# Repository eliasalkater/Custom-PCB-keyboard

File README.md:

# Custom-Mechanical-keyboard

Project: Custom Mechanical Keyboard

Goal: Design and build a fully functional mechanical keyboard, including a custom PCB and a custom 3D-printed case, designed to increase efficiency while programming.

Constraints:

    -Must be USB-C
    -Custom PCB
    -Custom case
    -3D printable
    -Reasonable cost
    -Functional firmware
    -Must be possible to manufacture with the tools available to me (JLCPCB)

A successful project is a keyboard where every key registers correctly, the PCB operates reliably, the case can be manufactured without significant post-processing, and the PCB, plate and case fit together without modification.

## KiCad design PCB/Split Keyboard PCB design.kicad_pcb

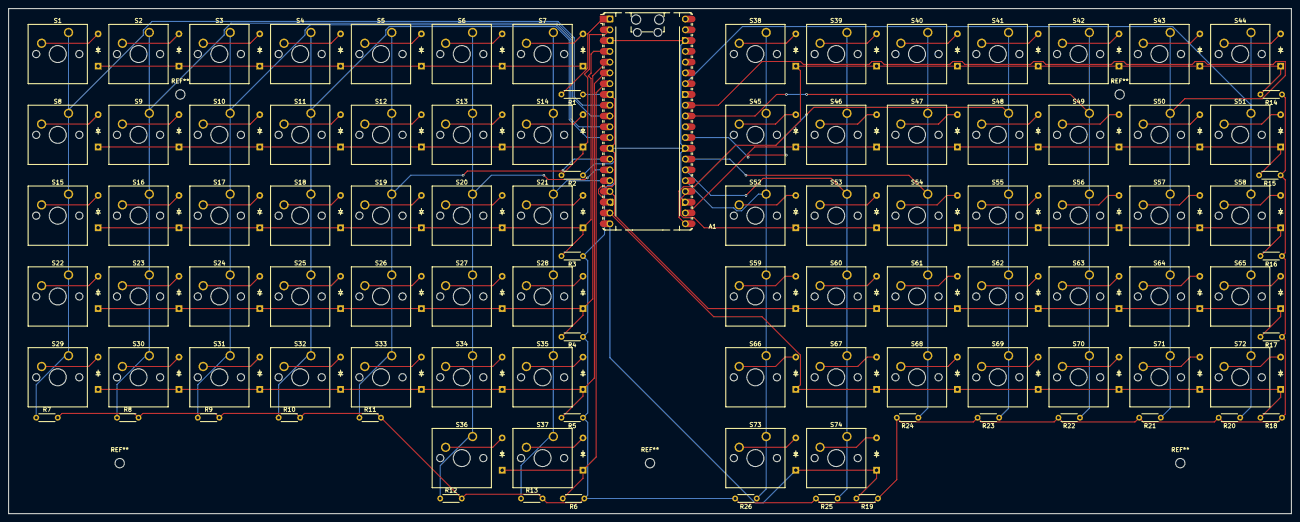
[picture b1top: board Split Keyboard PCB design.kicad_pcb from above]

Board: 2 copper layers, 302.4 x 119.1 mm, 175 parts (0 on the bottom side), 101 nets.

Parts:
A1: RaspberryPi_Pico; RaspberryPi_Pico_Common_Unspecified
D1, D2, D3, D4, D5, D6, D7, D8, D9, D10, D11, D12, D13, D14, D15, D16, D17, D18, D19, D20, D21, D22, D23, D24, D25, D26, D27, D28, D29, D30, D31, D32, D33, D34, D35, D36, D37, D38, D39, D40, D41, D42, D43, D44, D45, D46, D47, D48, D49, D50, D51, D52, D53, D54, D55, D56, D57, D58, D59, D60, D61, D62, D63, D64, D65, D66, D67, D68, D69, D70, D71, D72, D73, D74: Diode_DO-35
R1, R2, R3, R4, R5, R6, R7, R8, R9, R10, R11, R12, R13, R14, R15, R16, R17, R18, R19, R20, R21, R22, R23, R24, R25, R26: Resistor; R_Axial_DIN0204_L3.6mm_D1.6mm_P5.08mm_Horizontal
S1, S2, S3, S4, S5, S6, S7, S8, S9, S10, S11, S12, S13, S14, S15, S16, S17, S18, S19, S20, S21, S22, S23, S24, S25, S26, S27, S28, S29, S30, S31, S32, S33, S34, S35, S36, S37, S38, S39, S40, S41, S42, S43, S44, S45, S46, S47, S48, S49, S50, S51, S52, S53, S54, S55, S56, S57, S58, S59, S60, S61, S62, S63, S64, S65, S66, S67, S68, S69, S70, S71, S72, S73, S74: SW_Cherry_MX_1.00u_PCB

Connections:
Col 1: A1.9 (GPIO6), R7.1, S1.1, S8.1, S15.1, S22.1, S29.1
Col 2: A1.10 (GPIO7), R8.1, S2.1, S9.1, S16.1, S23.1, S30.1
Col 3: A1.11 (GPIO8), R9.1, S3.1, S10.1, S17.1, S24.1, S31.1
Col 4: A1.12 (GPIO9), R10.1, S4.1, S11.1, S18.1, S25.1, S32.1
Col 5: A1.14 (GPIO10), R11.1, S5.1, S12.1, S19.1, S26.1, S33.1
Col 6: A1.15 (GPIO11), R12.1, S6.1, S13.1, S20.1, S27.1, S34.1, S36.1
Col 7: A1.16 (GPIO12), R13.1, S7.1, S14.1, S21.1, S28.1, S35.1, S37.1
Col 8: A1.25 (GPIO19), R26.1, S38.1, S45.1, S52.1, S59.1, S66.1, S73.1
Col 9: A1.26 (GPIO20), R25.1, S39.1, S46.1, S53.1, S60.1, S67.1, S74.1
Col 10: A1.27 (GPIO21), R24.1, S40.1, S47.1, S54.1, S61.1, S68.1
Col 11: A1.29 (GPIO22), R23.1, S41.1, S48.1, S55.1, S62.1, S69.1
Col 12: A1.31 (GPIO26_ADC0), R22.1, S42.1, S49.1, S56.1, S63.1, S70.1
Col 13: A1.32 (GPIO27_ADC1), R21.1, S43.1, S50.1, S57.1, S64.1, S71.1
Col 14: A1.34 (GPIO28_ADC2), R20.1, S44.1, S51.1, S58.1, S65.1, S72.1
GND: A1.3 (GND), A1.8 (GND), A1.13 (GND), A1.18 (GND), A1.23 (GND), A1.28 (GND), A1.38 (GND), R1.1, R2.1, R3.1, R4.1, R5.1, R6.1, R7.2, R8.2, R9.2, R10.2, R11.2, R12.2, R13.2, R14.1, R15.1, R16.1, R17.1, R18.1, R19.1, R20.2, R21.2, R22.2, R23.2, R24.2, R25.2, R26.2
unnamed: D1.2 (A), S1.2
unnamed: D2.2 (A), S2.2
unnamed: D3.2 (A), S3.2
unnamed: D4.2 (A), S4.2
unnamed: D5.2 (A), S5.2
unnamed: D6.2 (A), S6.2
unnamed: D7.2 (A), S7.2
unnamed: D8.2 (A), S8.2
unnamed: D9.2 (A), S9.2
unnamed: D10.2 (A), S10.2
unnamed: D11.2 (A), S11.2
unnamed: D12.2 (A), S12.2
unnamed: D13.2 (A), S13.2
unnamed: D14.2 (A), S14.2
unnamed: D15.2 (A), S15.2
unnamed: D16.2 (A), S16.2
unnamed: D17.2 (A), S17.2
unnamed: D18.2 (A), S18.2
unnamed: D19.2 (A), S19.2
unnamed: D20.2 (A), S20.2
unnamed: D21.2 (A), S21.2
unnamed: D22.2 (A), S22.2
unnamed: D23.2 (A), S23.2
unnamed: D24.2 (A), S24.2
unnamed: D25.2 (A), S25.2
unnamed: D26.2 (A), S26.2
unnamed: D27.2 (A), S27.2
unnamed: D28.2 (A), S28.2
unnamed: D29.2 (A), S29.2
unnamed: D30.2 (A), S30.2
unnamed: D31.2 (A), S31.2
unnamed: D32.2 (A), S32.2
unnamed: D33.2 (A), S33.2
unnamed: D34.2 (A), S34.2
unnamed: D35.2 (A), S35.2
unnamed: D36.2 (A), S36.2
unnamed: D37.2 (A), S37.2
unnamed: D38.2 (A), S38.2
unnamed: D39.2 (A), S39.2
unnamed: D40.2 (A), S40.2
unnamed: D41.2 (A), S41.2
unnamed: D42.2 (A), S42.2
unnamed: D43.2 (A), S43.2
unnamed: D44.2 (A), S44.2
unnamed: D45.2 (A), S45.2
unnamed: D46.2 (A), S46.2
unnamed: D47.2 (A), S47.2
unnamed: D48.2 (A), S48.2
unnamed: D49.2 (A), S49.2
unnamed: D50.2 (A), S50.2
unnamed: D51.2 (A), S51.2
unnamed: D52.2 (A), S52.2
unnamed: D53.2 (A), S53.2
unnamed: D54.2 (A), S54.2
unnamed: D55.2 (A), S55.2
unnamed: D56.2 (A), S56.2
unnamed: D57.2 (A), S57.2
unnamed: D58.2 (A), S58.2
unnamed: D59.2 (A), S59.2
unnamed: D60.2 (A), S60.2
unnamed: D61.2 (A), S61.2
unnamed: D62.2 (A), S62.2
unnamed: D63.2 (A), S63.2
unnamed: D64.2 (A), S64.2
unnamed: D65.2 (A), S65.2
unnamed: D66.2 (A), S66.2
unnamed: D67.2 (A), S67.2
unnamed: D68.2 (A), S68.2
unnamed: D69.2 (A), S69.2
unnamed: D70.2 (A), S70.2
unnamed: D71.2 (A), S71.2
unnamed: D72.2 (A), S72.2
unnamed: D73.2 (A), S73.2
unnamed: D74.2 (A), S74.2
Row 1: A1.1 (GPIO0), D1.1 (K), D2.1 (K), D3.1 (K), D4.1 (K), D5.1 (K), D6.1 (K), D7.1 (K), R1.2
Row 2: A1.2 (GPIO1), D8.1 (K), D9.1 (K), D10.1 (K), D11.1 (K), D12.1 (K), D13.1 (K), D14.1 (K), R2.2
Row 3: A1.4 (GPIO2), D15.1 (K), D16.1 (K), D17.1 (K), D18.1 (K), D19.1 (K), D20.1 (K), D21.1 (K), R3.2
Row 4: A1.5 (GPIO3), D22.1 (K), D23.1 (K), D24.1 (K), D25.1 (K), D26.1 (K), D27.1 (K), D28.1 (K), R4.2
Row 5: A1.6 (GPIO4), D29.1 (K), D30.1 (K), D31.1 (K), D32.1 (K), D33.1 (K), D34.1 (K), D35.1 (K), R5.2
Row 6: A1.7 (GPIO5), D36.1 (K), D37.1 (K), R6.2
Row 7: A1.21 (GPIO16), D38.1 (K), D39.1 (K), D40.1 (K), D41.1 (K), D42.1 (K), D43.1 (K), D44.1 (K), R14.2
Row 8: A1.22 (GPIO17), D45.1 (K), D46.1 (K), D47.1 (K), D48.1 (K), D49.1 (K), D50.1 (K), D51.1 (K), R15.2
Row 9: A1.24 (GPIO18), D52.1 (K), D53.1 (K), D54.1 (K), D55.1 (K), D56.1 (K), D57.1 (K), D58.1 (K), R16.2
Row 10: A1.17 (GPIO13), D59.1 (K), D60.1 (K), D61.1 (K), D62.1 (K), D63.1 (K), D64.1 (K), D65.1 (K), R17.2
Row 11: A1.19 (GPIO14), D66.1 (K), D67.1 (K), D68.1 (K), D69.1 (K), D70.1 (K), D71.1 (K), D72.1 (K), R18.2
Row 12: A1.20 (GPIO15), D73.1 (K), D74.1 (K), R19.2
